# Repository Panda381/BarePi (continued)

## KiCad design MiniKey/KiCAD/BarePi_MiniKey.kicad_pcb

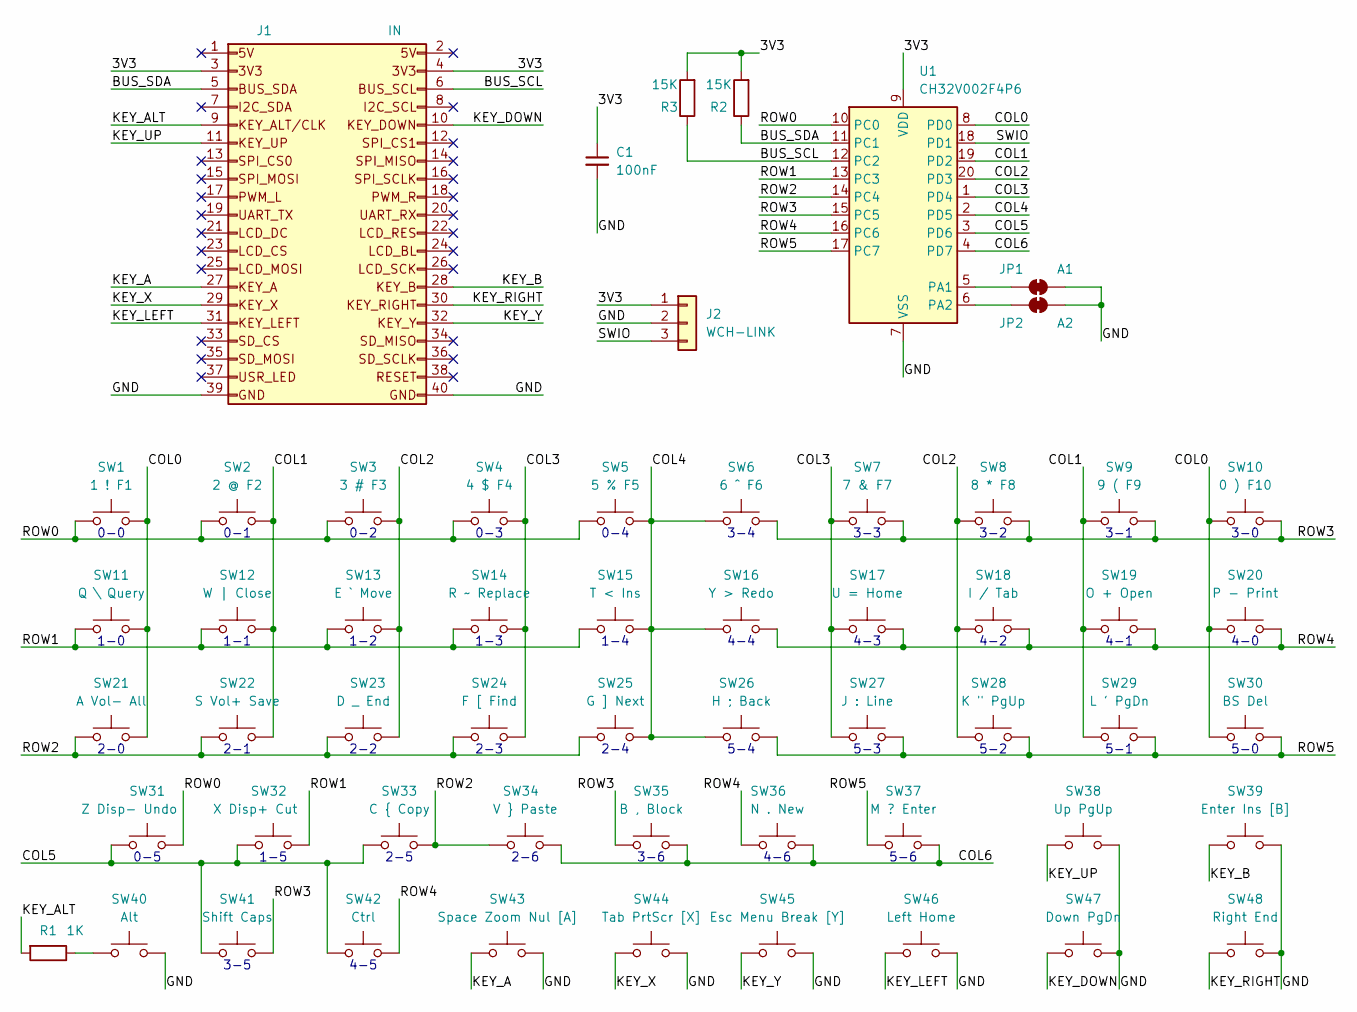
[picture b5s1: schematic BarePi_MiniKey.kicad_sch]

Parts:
C1: 100nF; C_1210_3225Metric_Pad1.33x2.70mm_HandSolder
J1: IN; Raspberry_IN_PinHeader_2x20_P2.54mm_Horizontal
J2: WCH-LINK; Raspberry_PinHeader_1x03_P2.54mm_Horizontal
JP1: A1; SolderJumper-2_P1.3mm_Bridged2Bar_RoundedPad1.0x1.5mm
JP2: A2; SolderJumper-2_P1.3mm_Bridged2Bar_RoundedPad1.0x1.5mm
R1: 1K; R_0805_2012Metric_Pad1.20x1.40mm_HandSolder
R2, R3: 15K; R_1206_3216Metric_Pad1.30x1.75mm_HandSolder
SW1: 1 ! F1; SW_PUSH_6mm
SW2: 2 @ F2; SW_PUSH_6mm
SW3: 3 # F3; SW_PUSH_6mm
SW4: 4 $ F4; SW_PUSH_6mm
SW5: 5 % F5; SW_PUSH_6mm
SW6: 6 ^ F6; SW_PUSH_6mm
SW7: 7 & F7; SW_PUSH_6mm
SW8: 8 * F8; SW_PUSH_6mm
SW9: 9 ( F9; SW_PUSH_6mm
SW10: 0 ) F10; SW_PUSH_6mm
SW11: Q \ Query; SW_PUSH_6mm
SW12: W | Close; SW_PUSH_6mm
SW13: E ` Move; SW_PUSH_6mm
SW14: R ~ Replace; SW_PUSH_6mm
SW15: T < Ins; SW_PUSH_6mm
SW16: Y > Redo; SW_PUSH_6mm
SW17: U = Home; SW_PUSH_6mm
SW18: I / Tab; SW_PUSH_6mm
SW19: O + Open; SW_PUSH_6mm
SW20: P - Print; SW_PUSH_6mm
SW21: A Vol- All; SW_PUSH_6mm
SW22: S Vol+ Save; SW_PUSH_6mm
SW23: D _ End; SW_PUSH_6mm
SW24: F [ Find; SW_PUSH_6mm
SW25: G ] Next; SW_PUSH_6mm
SW26: H ; Back; SW_PUSH_6mm
SW27: J : Line; SW_PUSH_6mm
SW28: K " PgUp; SW_PUSH_6mm
SW29: L ' PgDn; SW_PUSH_6mm
SW30: BS Del; SW_PUSH_6mm
SW31: Z Disp- Undo; SW_PUSH_6mm
SW32: X Disp+ Cut; SW_PUSH_6mm
SW33: C { Copy; SW_PUSH_6mm
SW34: V } Paste; SW_PUSH_6mm
SW35: B , Block; SW_PUSH_6mm
SW36: N . New; SW_PUSH_6mm
SW37: M ? Enter; SW_PUSH_6mm
SW38: Up PgUp; SW_PUSH_6mm
SW39: Enter Ins [B]; SW_PUSH_6mm
SW40: Alt; SW_PUSH_6mm
SW41: Shift Caps; SW_PUSH_6mm
SW42: Ctrl; SW_PUSH_6mm
SW43: Space Zoom Nul [A]; SW_PUSH_6mm
SW44: Tab PrtScr [X]; SW_PUSH_6mm
SW45: Esc Menu Break [Y]; SW_PUSH_6mm
SW46: Left Home; SW_PUSH_6mm
SW47: Down PgDn; SW_PUSH_6mm
SW48: Right End; SW_PUSH_6mm
U1: CH32V002F4P6; Raspberry_TSSOP-20_4.4x6.5mm_P0.65mm

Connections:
/3V3: C1.1, J1.3, J1.4, J2.1, R2.2, R3.2, U1.9 (VDD)
/BUS_SCL: J1.6, R3.1, U1.12 (PC2)
/BUS_SDA: J1.5, R2.1, U1.11 (PC1)
/COL0: SW1.2, SW10.1, SW11.2, SW20.1, SW21.2, SW30.1, U1.8 (PD0)
/COL1: SW2.2, SW9.1, SW12.2, SW19.1, SW22.2, SW29.1, U1.19 (PD2)
/COL2: SW3.2, SW8.1, SW13.2, SW18.1, SW23.2, SW28.1, U1.20 (PD3)
/COL3: SW4.2, SW7.1, SW14.2, SW17.1, SW24.2, SW27.1, U1.1 (PD4)
/COL4: SW5.2, SW6.1, SW15.2, SW16.1, SW25.2, SW26.1, U1.2 (PD5)
/COL5: SW31.1, SW32.1, SW33.1, SW41.1, SW42.1, U1.3 (PD6)
/COL6: SW34.2, SW35.2, SW36.2, SW37.2, U1.4 (PD7)
/GND: C1.2, J1.39, J1.40, J2.2, JP1.2 (B), JP2.2 (B), SW38.2, SW39.2, SW40.2, SW43.2, SW44.2, SW45.2, SW46.2, SW47.2, SW48.2, U1.7 (VSS)
/KEY_A: J1.27, SW43.1
/KEY_ALT: J1.9, R1.2
/KEY_B: J1.28, SW39.1
/KEY_DOWN: J1.10, SW47.1
/KEY_LEFT: J1.31, SW46.1
/KEY_RIGHT: J1.30, SW48.1
/KEY_UP: J1.11, SW38.1
/KEY_X: J1.29, SW44.1
/KEY_Y: J1.32, SW45.1
/ROW0: SW1.1, SW2.1, SW3.1, SW4.1, SW5.1, SW31.2, U1.10 (PC0)
/ROW1: SW11.1, SW12.1, SW13.1, SW14.1, SW15.1, SW32.2, U1.13 (PC3)
/ROW2: SW21.1, SW22.1, SW23.1, SW24.1, SW25.1, SW33.2, SW34.1, U1.14 (PC4)
/ROW3: SW6.2, SW7.2, SW8.2, SW9.2, SW10.2, SW35.1, SW41.2, U1.15 (PC5)
/ROW4: SW16.2, SW17.2, SW18.2, SW19.2, SW20.2, SW36.1, SW42.2, U1.16 (PC6)
/ROW5: SW26.2, SW27.2, SW28.2, SW29.2, SW30.2, SW37.1, U1.17 (PC7)
/SWIO: J2.3, U1.18 (PD1)
unnamed: JP1.1 (A), U1.5 (PA1)
unnamed: JP2.1 (A), U1.6 (PA2)
unnamed: R1.1, SW40.1

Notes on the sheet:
2-2
0-5
2-0
1-0
5-2
5-1
2-3
0-3
3-4
4-6
1-1
2-6
4-4
0-0
5-0
3-1
5-6
5-3
1-3
3-6
2-1
3-0
1-4
2-5
5-4
0-1
4-3
4-1
0-4
4-0
4-2
4-5
3-3
0-2
3-5
3-2
2-4
1-2
1-5

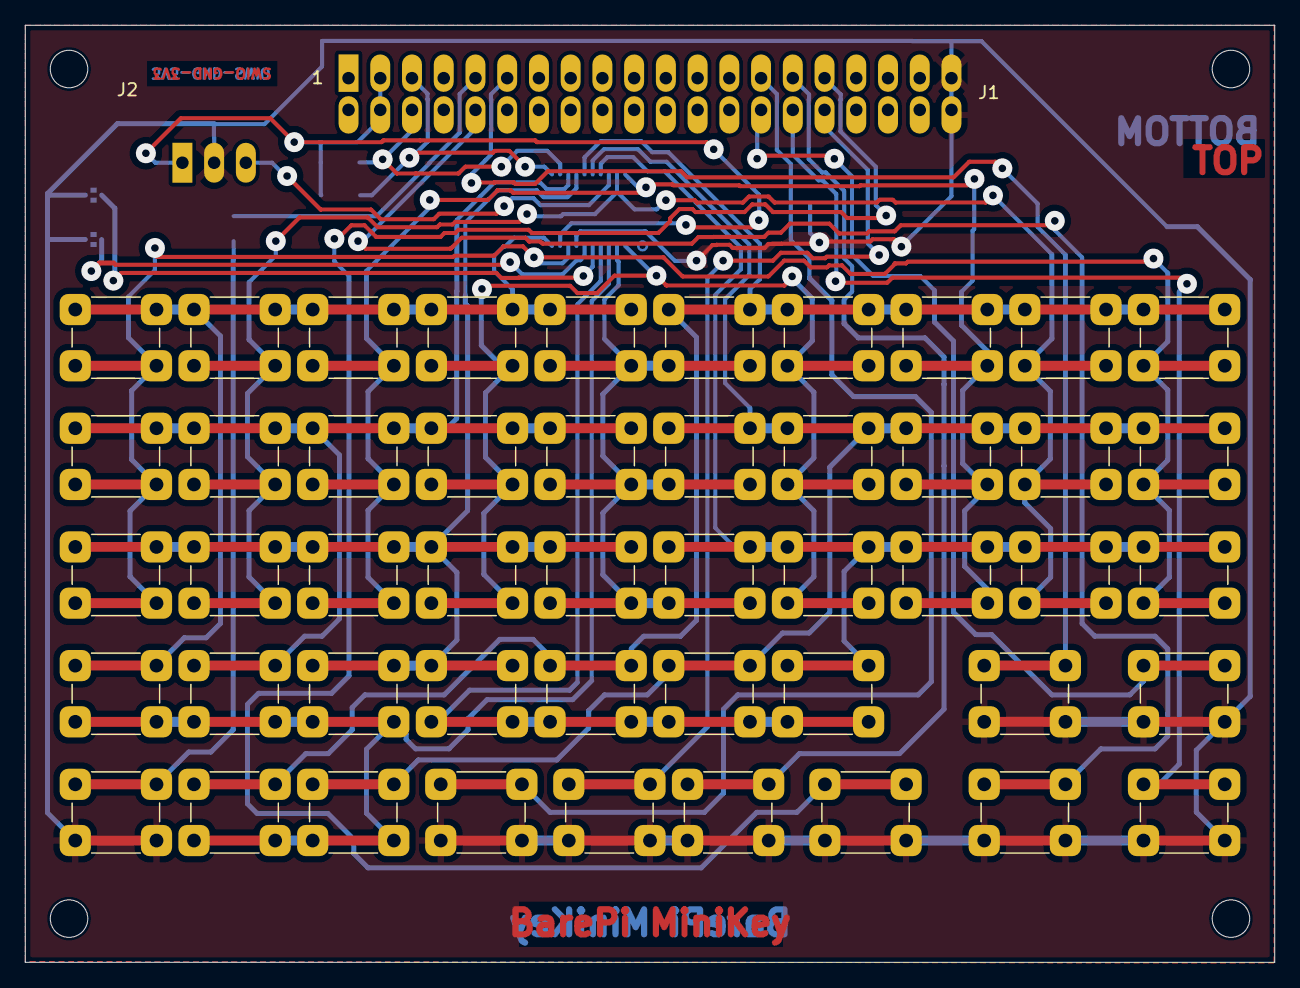
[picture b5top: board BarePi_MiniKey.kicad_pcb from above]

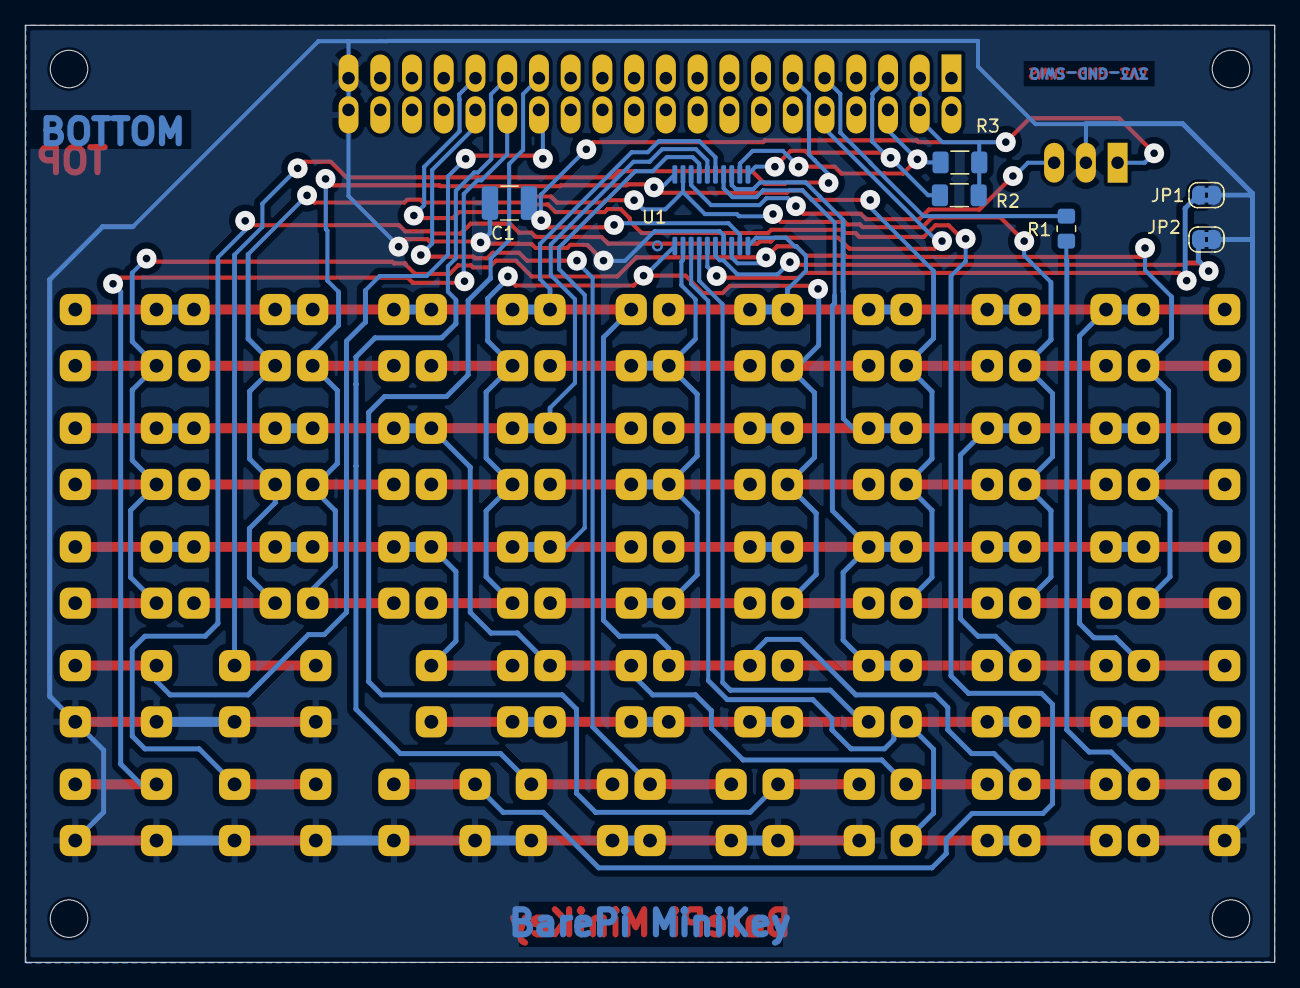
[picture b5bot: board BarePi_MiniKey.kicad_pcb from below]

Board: 2 copper layers, 100.0 x 75.0 mm, 57 parts (7 on the bottom side), 30 nets.

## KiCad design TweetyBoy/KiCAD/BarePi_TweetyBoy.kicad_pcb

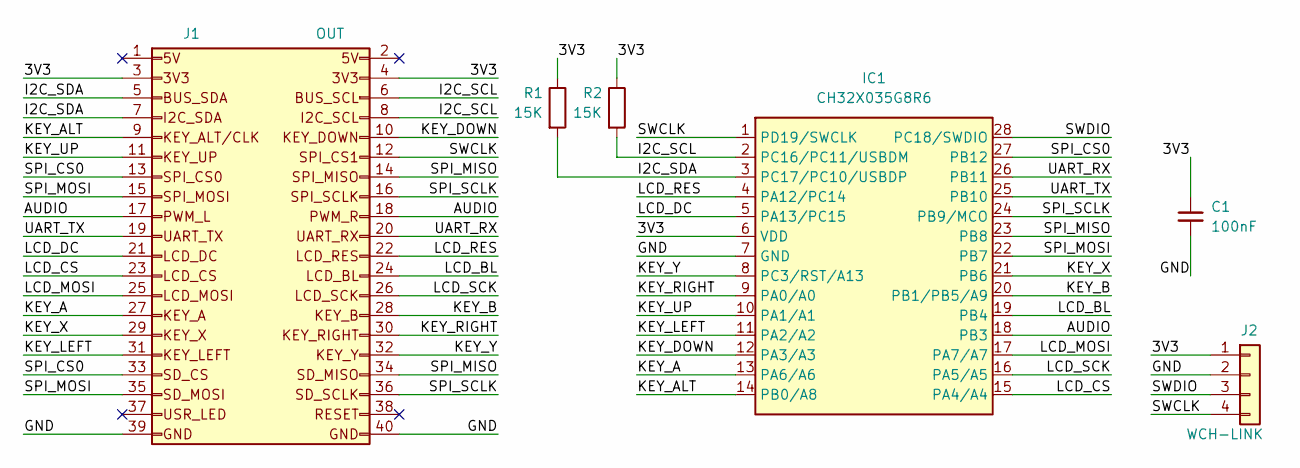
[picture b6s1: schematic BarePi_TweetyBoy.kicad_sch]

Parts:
C1: 100nF; C_1206_3216Metric_Pad1.33x1.80mm_HandSolder
IC1: CH32X035G8R6; Raspberry_QSOP-28_3.9x9.9mm_P0.635mm
J1: OUT; Raspberry_OUT_PinSocket_2x20_P2.54mm_Horizontal
J2: WCH-LINK; Raspberry_PinHeader_1x04_P2.54mm_Horizontal
R1, R2: 15K; R_1206_3216Metric_Pad1.30x1.75mm_HandSolder

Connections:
/3V3: C1.1, IC1.6 (VDD), J1.3, J1.4, J2.1, R1.1, R2.1
/AUDIO: IC1.18 (PB3), J1.17, J1.18
/GND: C1.2, IC1.7 (GND), J1.39, J1.40, J2.2
/I2C_SCL: IC1.2 (PC16/PC11/USBDM), J1.6, J1.8, R2.2
/I2C_SDA: IC1.3 (PC17/PC10/USBDP), J1.5, J1.7, R1.2
/KEY_A: IC1.13 (PA6/A6), J1.27
/KEY_ALT: IC1.14 (PB0/A8), J1.9
/KEY_B: IC1.20 (PB1/PB5/A9), J1.28
/KEY_DOWN: IC1.12 (PA3/A3), J1.10
/KEY_LEFT: IC1.11 (PA2/A2), J1.31
/KEY_RIGHT: IC1.9 (PA0/A0), J1.30
/KEY_UP: IC1.10 (PA1/A1), J1.11
/KEY_X: IC1.21 (PB6), J1.29
/KEY_Y: IC1.8 (PC3/RST/A13), J1.32
/LCD_BL: IC1.19 (PB4), J1.24
/LCD_CS: IC1.15 (PA4/A4), J1.23
/LCD_DC: IC1.5 (PA13/PC15), J1.21
/LCD_MOSI: IC1.17 (PA7/A7), J1.25
/LCD_RES: IC1.4 (PA12/PC14), J1.22
/LCD_SCK: IC1.16 (PA5/A5), J1.26
/SPI_CS0: IC1.27 (PB12), J1.13, J1.33
/SPI_MISO: IC1.23 (PB8), J1.14, J1.34
/SPI_MOSI: IC1.22 (PB7), J1.15, J1.35
/SPI_SCLK: IC1.24 (PB9/MCO), J1.16, J1.36
/SWCLK: IC1.1 (PD19/SWCLK), J1.12, J2.4
/SWDIO: IC1.28 (PC18/SWDIO), J2.3
/UART_RX: IC1.26 (PB11), J1.20
/UART_TX: IC1.25 (PB10), J1.19

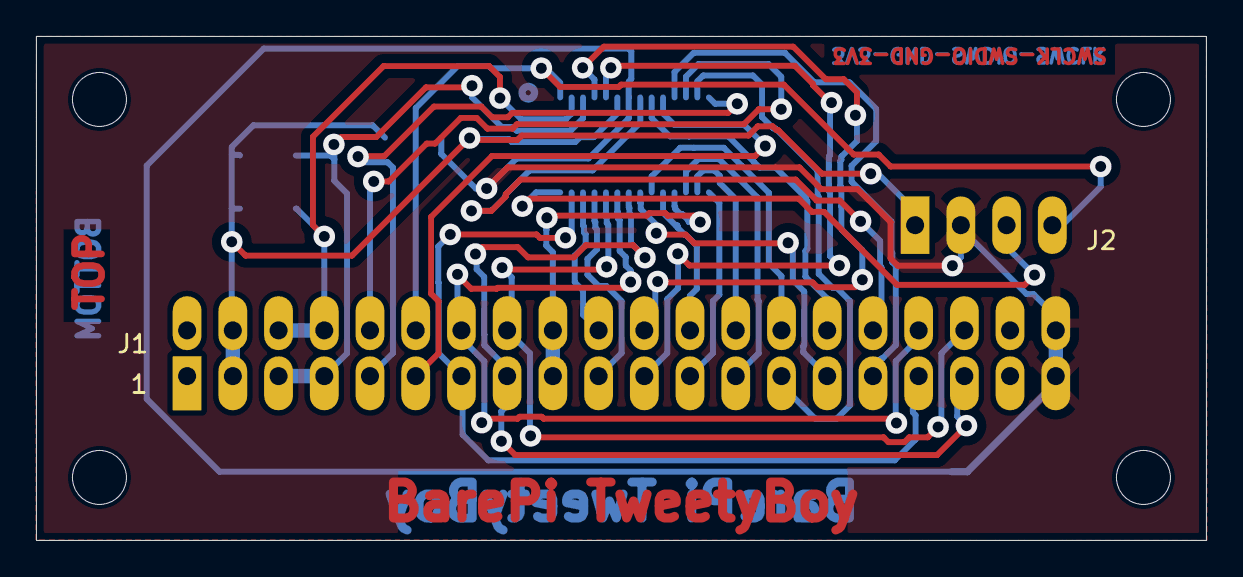
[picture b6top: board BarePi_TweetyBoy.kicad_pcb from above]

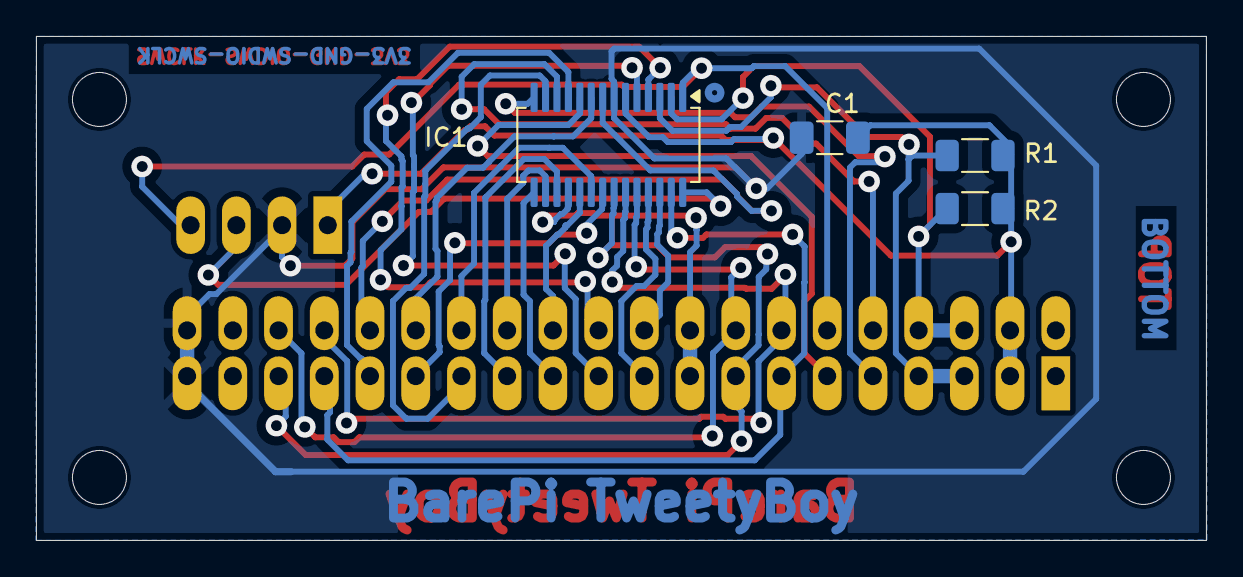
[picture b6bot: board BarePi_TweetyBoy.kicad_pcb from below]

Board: 2 copper layers, 65.0 x 28.0 mm, 6 parts (4 on the bottom side), 28 nets.

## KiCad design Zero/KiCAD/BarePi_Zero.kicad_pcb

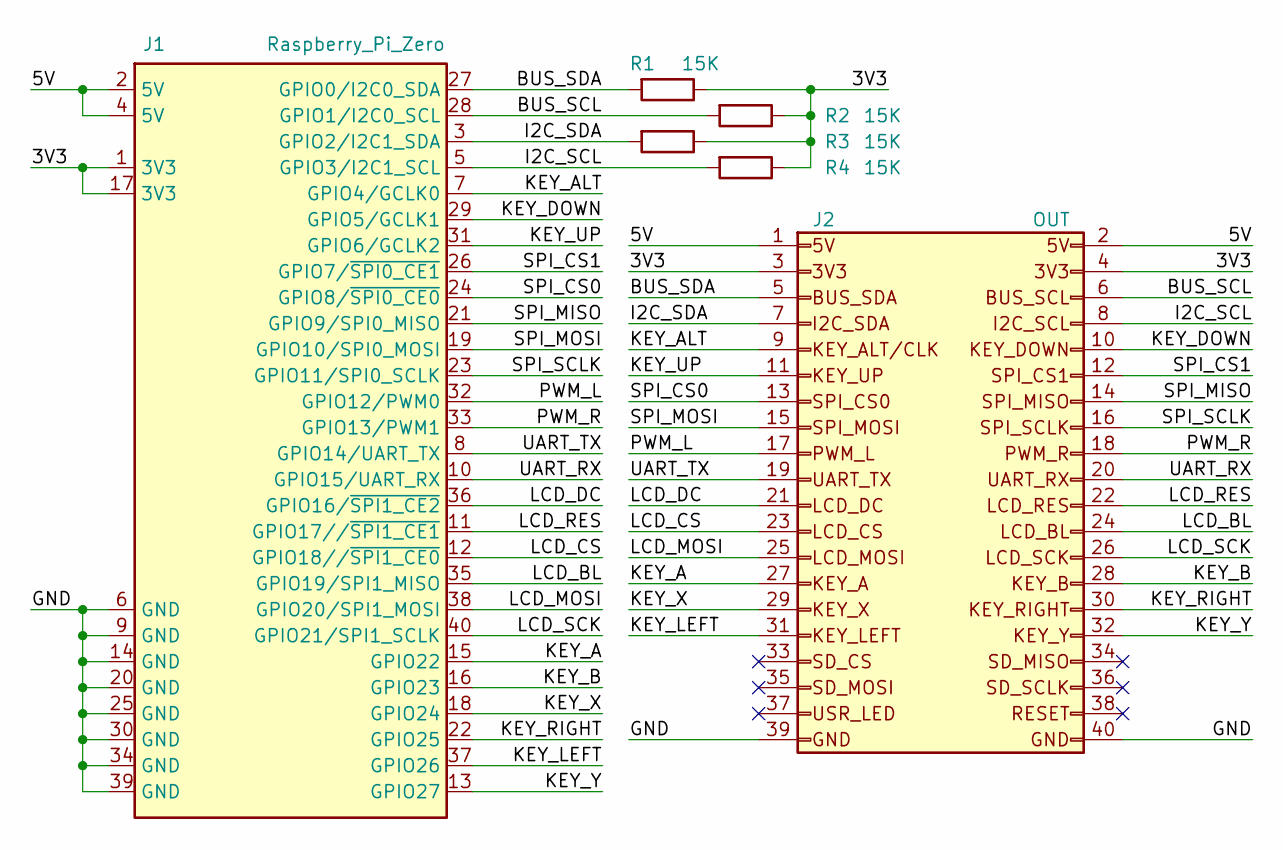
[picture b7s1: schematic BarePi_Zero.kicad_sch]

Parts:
J1: Raspberry_Pi_Zero; Raspberry_Pi_Zero_Socketed_THT_FaceDown_MountingHoles
J2: OUT; Raspberry_OUT_PinSocket_2x20_P2.54mm_Horizontal
R1, R2, R3, R4: 15K; R_1206_3216Metric_Pad1.30x1.75mm_HandSolder

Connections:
/3V3: J1.1 (3V3), J1.17 (3V3), J2.3, J2.4, R1.1, R2.1, R3.1, R4.1
/5V: J1.2 (5V), J1.4 (5V), J2.1, J2.2
/BUS_SCL: J1.28 (GPIO1/I2C0_SCL), J2.6, R2.2
/BUS_SDA: J1.27 (GPIO0/I2C0_SDA), J2.5, R1.2
/GND: J1.6 (GND), J1.9 (GND), J1.14 (GND), J1.20 (GND), J1.25 (GND), J1.30 (GND), J1.34 (GND), J1.39 (GND), J2.39, J2.40
/I2C_SCL: J1.5 (GPIO3/I2C1_SCL), J2.8, R4.2
/I2C_SDA: J1.3 (GPIO2/I2C1_SDA), J2.7, R3.2
/KEY_A: J1.15 (GPIO22), J2.27
/KEY_ALT: J1.7 (GPIO4/GCLK0), J2.9
/KEY_B: J1.16 (GPIO23), J2.28
/KEY_DOWN: J1.29 (GPIO5/GCLK1), J2.10
/KEY_LEFT: J1.37 (GPIO26), J2.31
/KEY_RIGHT: J1.22 (GPIO25), J2.30
/KEY_UP: J1.31 (GPIO6/GCLK2), J2.11
/KEY_X: J1.18 (GPIO24), J2.29
/KEY_Y: J1.13 (GPIO27), J2.32
/LCD_BL: J1.35 (GPIO19/SPI1_MISO), J2.24
/LCD_CS: J1.12 (GPIO18//~SPI1_CE0), J2.23
/LCD_DC: J1.36 (GPIO16/~SPI1_CE2), J2.21
/LCD_MOSI: J1.38 (GPIO20/SPI1_MOSI), J2.25
/LCD_RES: J1.11 (GPIO17//~SPI1_CE1), J2.22
/LCD_SCK: J1.40 (GPIO21/SPI1_SCLK), J2.26
/PWM_L: J1.32 (GPIO12/PWM0), J2.17
/PWM_R: J1.33 (GPIO13/PWM1), J2.18
/SPI_CS0: J1.24 (GPIO8/~SPI0_CE0), J2.13
/SPI_CS1: J1.26 (GPIO7/~SPI0_CE1), J2.12
/SPI_MISO: J1.21 (GPIO9/SPI0_MISO), J2.14
/SPI_MOSI: J1.19 (GPIO10/SPI0_MOSI), J2.15
/SPI_SCLK: J1.23 (GPIO11/SPI0_SCLK), J2.16
/UART_RX: J1.10 (GPIO15/UART_RX), J2.20
/UART_TX: J1.8 (GPIO14/UART_TX), J2.19

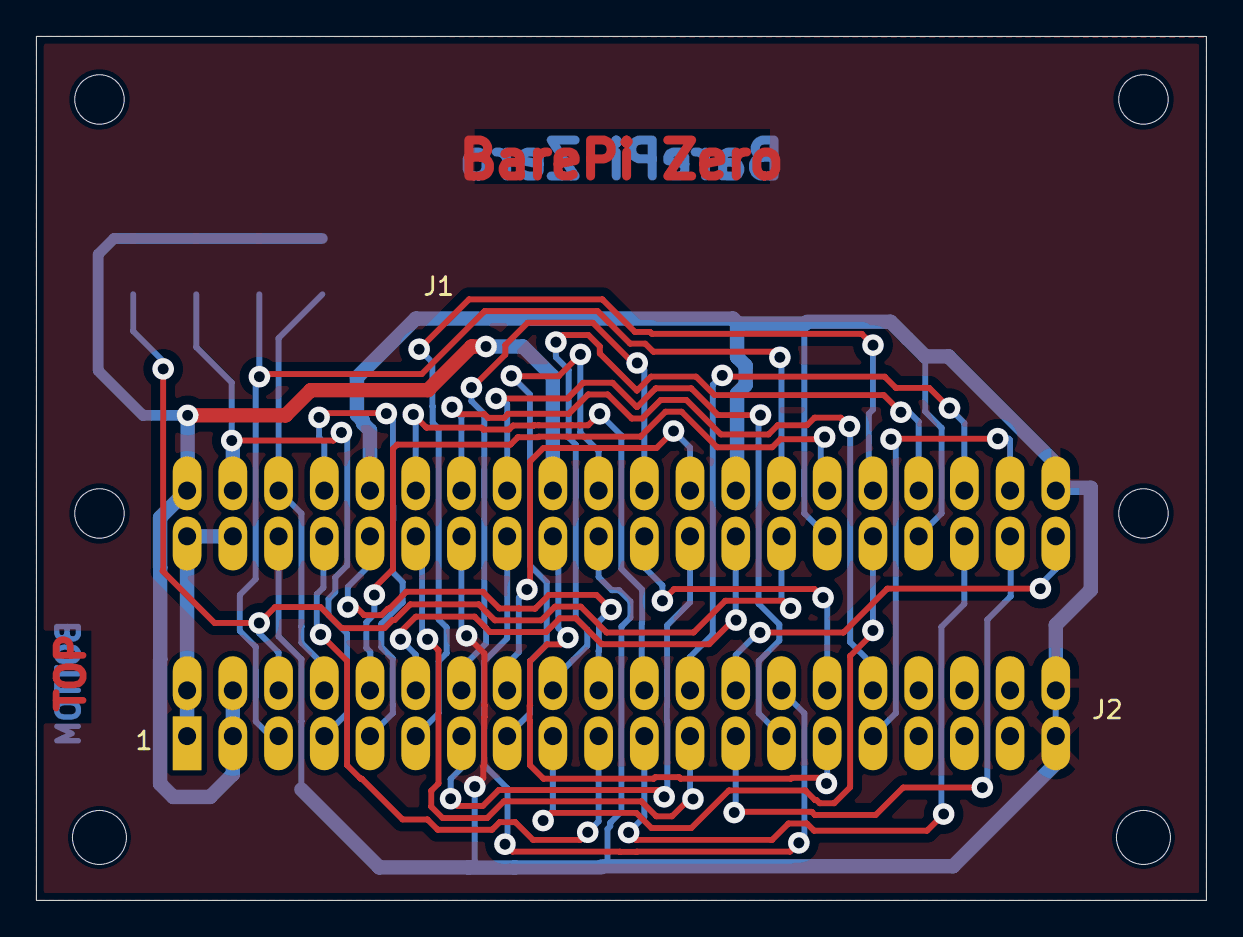
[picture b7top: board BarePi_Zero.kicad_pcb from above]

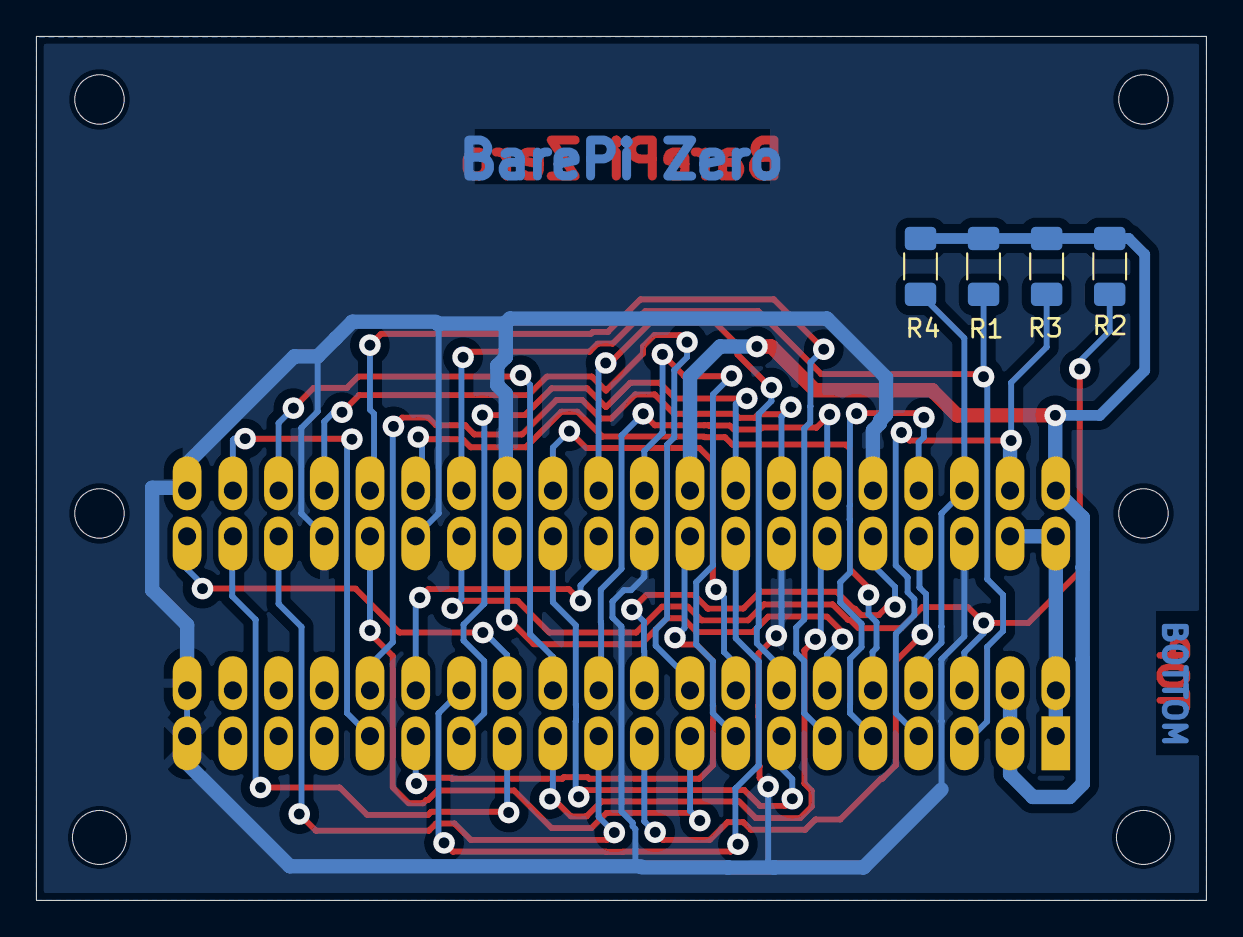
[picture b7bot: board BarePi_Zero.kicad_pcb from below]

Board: 2 copper layers, 65.0 x 48.0 mm, 6 parts (4 on the bottom side), 31 nets.

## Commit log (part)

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2026-06-03 init
